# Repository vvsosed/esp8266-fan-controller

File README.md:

# fan_controller

ESP8266 firmware that drives three 4-pin PWM PC fans from a radiator's inlet temperature, meters the water flow and the heat the radiator sheds, keeps an energy total, reports each fan's RPM over serial, serves a status page over Wi-Fi, and shares its fan curve and readings over MQTT.

Hardware design, wiring and parts list: see [`docs/esp8266-fan-controller-research.md`](docs/esp8266-fan-controller-research.md).

---

## Quick reference

Run all commands from inside the sketch folder.

| Task | Command |
|---|---|
| Compile | `./build.sh` |
| Compile + flash | `./build.sh --upload` |
| Flash last build | `arduino-cli upload .` |
| Serial monitor | `arduino-cli monitor -p $PORT --config baudrate=115200` |
| Export `.bin` to `./build` | `./build.sh -e` |
| Clean rebuild | `./build.sh --clean` |
| Find connected boards | `arduino-cli board list` |
| Update cores/libraries | `arduino-cli update && arduino-cli upgrade` |

These short forms work after the one-time `board attach` step in [Setup](#4-attach-board-and-port-to-the-sketch). Without it, add `-b $FQBN` (and `-p $PORT` for upload).

`./build.sh` writes the current git commit into `git_hash.h`, then runs `arduino-cli compile` with any extra arguments you give it. The commit shows in the status page footer. Plain `arduino-cli compile .` also builds, but the footer then shows `unknown`, or the commit from the last `./build.sh` run.

---

## Project layout

```
fan_controller/
├── fan_controller.ino   # firmware (folder and .ino names must match)
├── build.sh             # stamps the git commit into git_hash.h, then compiles
├── git_hash.h           # generated by build.sh; not committed
├── sketch.yaml          # default board + port, created by `board attach`; not committed
├── README.md
├── CLAUDE.md            # guidance for Claude Code
├── .gitignore
├── docs/
│   ├── esp8266-fan-controller-research.md   # hardware design, wiring, parts list
│   └── board/           # perfboard placement plan for a bare ESP-12F: `python3 page.py` regenerates board.html
├── hardware/
│   └── kicad/           # KiCad 10 project, generated: schematic, two-layer PCB, fab files in out/ (`python3 gen.py`)
├── mqtt-broker/         # throwaway Mosquitto in Docker for testing MQTT (Dockerfile + entrypoint.sh)
└── build/               # only if you export binaries (-e); not committed
```

---

## Hardware summary

| Signal | GPIO | Board label | Notes |
|---|---|---|---|
| PWM, all three fans | 12 | D6 | One NPN/MOSFET open-drain stage feeds every fan's pin 4, like a PWM splitter (inverted in firmware) |
| Fan 1 / 2 / 3 tach | 5 / 4 / 14 | D1 / D2 / D5 | 10 kΩ pull-up to **3.3 V** |
| Inlet and outlet DS18B20s, data | 2 | D4 | Both on one 1-Wire bus, 4.7 kΩ pull-up to 3.3 V. Which is which is set on the status page ([water loop](#water-loop-flow-heat-and-energy)) |
| Flow meter pulses | 13 | D7 | The meter runs on 12 V and its pulses swing that high, so they go through an inverting NPN: 10 kΩ into the base, collector to D7 with a 10 kΩ pull-up to 3.3 V. The firmware also enables D7's internal pull-up, so a disconnected pin counts nothing |
| Fans' 12 V switch | 16 | D0 | NPN + P-MOSFET high-side switch, 10 kΩ pull-up to 3.3 V. High or undriven = fans powered |

Fans run on a separate 12 V supply, switched on and off by D0 ([wiring](docs/esp8266-fan-controller-research.md#5-wiring-per-channel)). The flow meter takes its 12 V before that switch, so it keeps counting with the fans off. All grounds must be common.

D8 (GPIO15) is the only free pin. It must be low at boot, so nothing wired to it may pull it high.

---

## Ordering the PCB

`hardware/kicad/` is a KiCad 10 project with the controller's schematic and a two-layer 70 × 50 mm board: the circuit of the
[perfboard plan](https://vvsosed.github.io/esp8266-fan-controller/board/board.html) built around a bare ESP-12F, plus two
protections the perfboard never had, a resettable fuse on the 12 V input and a reverse-polarity diode behind it. Everything
there is generated by scripts, and the committed files are the current output, so ordering needs no KiCad.

**To order**: upload `hardware/kicad/out/gerbers.zip` (Gerbers, drill file and job file) to any two-layer service, such as
JLCPCB, PCBWay or Aisler, and take the defaults: 2 layers, 1.6 mm FR-4, any finish, any mask colour. The design keeps
0.25 mm clearance, 0.3 mm tracks and 0.8/0.4 mm vias, two to three times every basic service's minimum, so no option needs
changing.

**To populate**: `hardware/kicad/out/bom.csv` lists every part, and `out/board-top.png`, `out/board-bottom.png` and
`out/schematic.pdf` show where it goes. Beyond the [parts list](docs/esp8266-fan-controller-research.md#6-parts-list), the
bare ESP-12F and the Mini-360 buck module (set it to 3.3 V before it goes in) that the perfboard plan already uses, buy an
MF-R250 polyfuse (2.5 A hold, radial, 5.1 mm lead pitch) for F1 and a 1N5401 (3 A, DO-201AD) for D2. D2 sits across the
fused input, so a reversed supply trips the fuse instead of the board. The silkscreen names every header pin and marks the
diodes' cathodes.

**To change it**: the circuit lives in `docs/board/data.py` (the netlist is derived from the perfboard plan) and every
position, track and label in `hardware/kicad/layout.py`. `python3 hardware/kicad/gen.py` regenerates the project, runs ERC
and DRC and rewrites `out/` (`--quick` skips the exports); it needs KiCad 10 with its Python module and `kicad-cli` on the
path. `python3 -m unittest discover -s hardware/kicad/tests` runs the checks. Open `hardware/kicad/fan_controller.kicad_pro`
in KiCad to look around, but don't edit the generated files: the next run overwrites them.

---

## Setup (once per machine, Manjaro / Arch)

### 1. Install Arduino CLI and get serial port access

```bash
sudo pacman -S arduino-cli
sudo usermod -aG uucp $USER   # log out and back in afterwards
groups                        # should now list uucp
```

### 2. Install the ESP8266 core

```bash
arduino-cli config init
arduino-cli config add board_manager.additional_urls \
  https://arduino.esp8266.com/stable/package_esp8266com_index.json
arduino-cli core update-index
arduino-cli core install esp8266:esp8266
```

### 3. Install libraries

```bash
arduino-cli lib install OneWire DallasTemperature WiFiManager@2.0.17 PubSubClient@2.8.0
```

### 4. Attach board and port to the sketch

Set the board and port for your hardware:

```bash
export FQBN=esp8266:esp8266:d1_mini:xtal=160,baud=921600   # NodeMCU: esp8266:esp8266:nodemcuv2:...
export PORT=/dev/ttyUSB0                                   # check with: arduino-cli board list
```

| FQBN option | Meaning |
|---|---|
| `xtal=160` | CPU at 160 MHz (smoother software PWM) |
| `baud=921600` | Upload speed; use `115200` if uploads fail |
| `wipe=all` | Erase the entire flash on upload (use only when needed) |

List every option your board supports:

```bash
arduino-cli board details -b esp8266:esp8266:d1_mini
```

Save board and port into `sketch.yaml` so later commands need no flags:

```bash
arduino-cli board attach -p $PORT -b $FQBN .
```

### 5. Resolve `.local` names

The board announces itself over mDNS. Linux resolves `.local` names only when the Avahi daemon runs and `nss-mdns` is hooked into name lookup. Manjaro usually ships both packages with the daemon disabled.

```bash
sudo pacman -S --needed avahi nss-mdns
grep '^hosts' /etc/nsswitch.conf      # must contain: mdns_minimal [NOTFOUND=return] before resolve
sudo systemctl enable --now avahi-daemon
getent hosts fan-controller-XXXXXX.local   # prints its IP once your PC and the board share a network
avahi-browse -rt _http._tcp                # lists every board on the network with its name and IP
```

If the `hosts:` line lacks `mdns_minimal`, edit it to look like this:

```
hosts: mymachines mdns_minimal [NOTFOUND=return] resolve [!UNAVAIL=return] files myhostname dns
```

Run the `sudo` lines in a normal terminal. Claude Code's `!` prefix can't answer the password prompt.

---

## Everyday tasks

### Compile

```bash
./build.sh                       # add -v for full compiler output
```

The build summary at the end shows flash and RAM usage.

### Flash

```bash
./build.sh --upload              # compile and flash in one step
arduino-cli upload .             # flash the last build without recompiling
```

Close the serial monitor first, because it holds the port.

### Serial monitor

```bash
arduino-cli monitor -p $PORT --config baudrate=115200
```

Exit with `Ctrl+C`. Expected output, once per second:

```
#3 +12.004 2026-10-19 03:12:58 In 31.2 Out 29.8 °C 2.10 L/min 280 W -> 60 % | Fan1 840 RPM Fan2 812 RPM Fan3 865 RPM
```

Each line starts with the boot number and the seconds since boot, then the local date and time once the board has the [time from the internet](#clock-and-timestamps). Then the inlet and outlet temperatures (a missing sensor prints `-127.0`), the flow, the heat (`-- W` until both sensors read) and the duty the curve gave.

A burst of garbage right after reset is normal: the ESP8266 bootloader prints at 74880 baud.

Lines starting with `*wm:` come from WiFiManager. Once the board joins your router it prints where to find the [status page](#wi-fi):

```
Web UI: http://192.168.1.42/  (http://fan-controller-1a2b3c.local/)
```

### Get the compiled binary

By default, builds go to the cache at `~/.cache/arduino/sketches/<HASH>/fan_controller.ino.bin` (older CLI versions use `/tmp/arduino/sketches/<HASH>/`).

```bash
./build.sh -e                             # copy binaries to ./build/<fqbn>/
./build.sh --output-dir ./out             # copy binaries to a directory of your choice
arduino-cli compile --show-properties . | grep '^build.path'   # print the cache path
```

To always export binaries:

```bash
arduino-cli config set sketch.always_export_binaries true
```

### Flash a `.bin` with esptool directly

This is useful for flashing a saved build without the sketch.

```bash
sudo pacman -S esptool
esptool.py --port $PORT --baud 460800 write_flash 0x0 build/*/fan_controller.ino.bin
```

### Flash over Wi-Fi from the browser

Once the board is on your network, it doesn't need the USB cable:

1. Run `./build.sh -e`. Commit first if you want a clean hash in the [footer](#status-page).
2. On the status page, open **Info / erase Wi-Fi** → **Update**, choose `build/esp8266.esp8266.d1_mini/fan_controller.ino.bin` and press **Update**.
3. The page says `Update successful. Device rebooting now...`, waits until the board answers again (about 20 s), then opens the status page. Check the version in the footer.

The fans run at 100 % during the reboot. The saved curve and Wi-Fi settings are kept. If the board isn't back within a minute, press RST once (twice opens the setup access point).

### Erase the flash completely

Use this before flashing if the board behaves oddly after flashing other firmware.

```bash
esptool.py --port $PORT erase_flash
# or, through Arduino CLI, during upload:
arduino-cli upload -b $FQBN,wipe=all -p $PORT .
```

### Identify the chip and flash size

```bash
esptool.py --port $PORT flash_id
```

### Change the fan curve

Use the form on the [status page](#status-page), or [MQTT](#mqtt): duty ramps linearly from the low % at the low temperature to the high % at the high temperature, and is clamped outside that range. **Save** applies it on the next 1 s cycle and stores it in flash, so it survives reboots. **Defaults** restores the values compiled into the firmware.

| Field | Default | Allowed |
|---|---|---|
| Ramp start / end (°C) | 21 / 30 | 0–100, start below end |
| Duty at start / end (%) | 20 / 100 | 0–100, start ≤ end, end at least 1 (0 → 0 % would keep the fans switched off) |

The defaults are `DEFAULT_CURVE` in `fan_controller.ino`:

```cpp
const Curve DEFAULT_CURVE = {21, 30, 20, 100};   // tLow °C, tHigh °C, pctMin %, pctMax %
```

Editing them only matters until a curve has been saved from the page; after that the saved curve wins until you press **Defaults** (or flash with `wipe=all`).

A missing inlet sensor and the boot period always run the fans at 100 % (`PCT_FAILSAFE`), even if the curve's maximum is lower.

### Water loop: flow, heat and energy

Two DS18B20s on the same 1-Wire bus measure the radiator's inlet (the warm water from the PC) and its outlet, and a Hall-effect flow meter (a YF-S401 or similar) counts the water through it. From those the board shows:

- **Heat**, in W: what the radiator sheds, `heat capacity × flow / 60 × (inlet − outlet)`. Positive while the water comes in warmer than it leaves; `—` on the page and `null` in the JSON while either sensor is missing.
- **Energy**, in kWh: the heat summed since the last **Reset** on the status page, which also shows when that was. It survives restarts, firmware updates and power cuts: the total goes to RTC memory every second and to a flash log of its own once an hour and on Reset, so a power cut loses under an hour of it. Serial prints `Energy: 123 Wh, from RTC` (or `from flash`) at boot and `Energy: reset` on Reset.
- **Flow**, in L/min.

The fan curve follows the **inlet**. Which physical sensor plays which role is a saved setting: the first sensor the board ever finds becomes the inlet, so a board upgraded with one sensor keeps regulating on it, and the next one found becomes the outlet. Open **Loop** on the status page to see both sensors' addresses, and press **Swap inlet/outlet** if they are the wrong way round. A missing inlet runs the fans at 100 %, as a missing sensor always has; a missing outlet only blanks the heat. While a sensor is missing the board looks at the bus once a minute, and a sensor it has never seen takes the vacant role: a newly plugged or replaced sensor is picked up without a reboot, while a sensor that is merely unplugged keeps its role until it is back. Serial prints the roles at boot and after every change: `Loop: 4186 J/(L·K), 5880 pulses/L; inlet 28ff…, outlet 28ff…`.

**Loop** also holds the two numbers the heat depends on. **Save** stores them in flash:

| Field | Default | Allowed | Notes |
|---|---|---|---|
| Water, J/(L·K) | 4186 | 100–20000 | The coolant's heat capacity per litre: water 4186, a 30 % glycol mix about 3900. Per litre, because the meter measures litres, so density is already in it |
| Flow meter, pulses/L | 5880 | 10–65535 | The YF-S401's figure; clones vary. To calibrate, run a measured amount of water through the meter at a steady rate while timing it, and compare the amount the board's flow implies (L/min × minutes) with what you measured: new value = old value × implied ÷ measured |
| Outlet offset, °C | 0 | −5 to 5 | Added to the outlet reading everywhere: page, JSON, serial, graphs and the heat. Two sensors rarely agree to better than 0.5 °C, and at 2 L/min each 0.1 °C of disagreement is 14 W of false heat. To set it, tape the two sensors together or put both in one glass of water, wait a minute for the readings to settle, and press **Match outlet to inlet**: the board saves the smoothed difference of the last cycles, so the heat reads zero while the two are at one temperature |

Over [MQTT](#mqtt) the readings travel in `status` (`tin`, `tout`, `flow`, `heat`, `wh`, `since`). For Home Assistant's energy dashboard, `wh / 1000` makes a `kWh` sensor with `device_class: energy` and `state_class: total`, with `last_reset` taken from `since`. Not `total_increasing`: the total is signed and falls while the heat is negative, which Home Assistant would take for a meter reset and count twice. The loop settings have no MQTT topics.

**Fans fully off.** Most fans don't stop at 0 % PWM; they drop to a minimum speed instead. So when the curve gives 0 %, the firmware switches off the fans' 12 V through D0:

- **When it happens:** set **Duty at start** to 0 %. The curve works in whole degrees and rounds, so the duty leaves 0 % at the first whole degree where it reaches 1 %. With ramp start 22 °C that's 23 °C. A very flat curve, rising less than ½ % per degree (say 22–80 °C → 0–20 %), leaves 0 % a degree or more later.
- **On:** the 12 V comes back on in the next 1 s cycle once the duty is above 0.
- **Off:** the temperature has to fall 0.5 °C below that point (`POWER_HYST_C`; below 22.5 °C in the example) and stay there for 10 s straight (`POWER_OFF_DELAY_S`). In between, the fans keep running at their minimum speed. Without this, sensor noise right at the threshold would switch the fans on and off.
- **Sensor glitch:** a failed reading runs the fans at 100 % for that one second only; then they're off again.

---

## Wi-Fi

Your network's name and password are never in the source. WiFiManager stores them in the ESP's own flash.

### First-time setup

1. Flash the board. With no network saved, it starts an access point named `fan-controller-XXXXXX`, where `XXXXXX` is its chip ID. The board answers to that name on the access point and on your network alike (`http://fan-controller-XXXXXX.local/`), so note it down. Every board gets its own name, so several can share one network.
2. Join it from a phone or laptop. The password is `AP_PASS` in `fan_controller.ino` (default `fancontrol`).
3. A setup page opens by itself (otherwise browse to `http://fan-controller-XXXXXX.local/` or `http://192.168.4.1/`). Pick your network, enter its password, Save.
4. The access point shuts down and the board joins your router. Serial prints the `Web UI:` line.

The fans keep following the temperature the whole time the access point is up.

### Status page

Open `http://fan-controller-XXXXXX.local/`, the same name as the setup access point (needs [mDNS on your PC](#5-resolve-local-names)), or the IP from serial. The page title and footer show the board's name. It shows the inlet and outlet temperatures, the flow, the heat and the fan duty, the energy total with its Reset button, and each fan's RPM, updating every 2 s, two graphs of the last hour, the [fan curve](#change-the-fan-curve) form, the [water loop](#water-loop-flow-heat-and-energy) settings, the [MQTT](#mqtt) broker settings, and links to the pages below. When the 12 V is [switched off](#change-the-fan-curve), the status line says `fans off`. The last two lines show the [uptime, boots and crashes](#uptime-boots-and-crashes).

**The graphs:**
- The first: inlet (red) and outlet (pale red) on the left °C axis, duty (blue) on the right % axis, as 10-second averages. Dashed lines mark the curve's ramp start and end temperatures.
- The second: heat (purple, W, left axis) and flow (green, L/min, right axis). Both axes fit the data and always include 0, where the heat axis has a dashed line.
- Gaps mean a sensor wasn't read; the heat line needs both.
- The history is kept in the board's RAM, so it starts empty after every reboot or flash.
- Inside the ramp, duty follows the inlet temperature linearly, so those two lines often lie on top of each other. They separate where the duty is clamped at its minimum or maximum.

| Page | Use |
|---|---|
| `/history.json` | The graph data, oldest first: `{"step":10,"tl":21,"th":30,"t":[31.2,null,…],"t2":[29.8,…],"w":[280,null,…],"f":[2.10,…],"d":[60,100,…]}` (`t` inlet, `t2` outlet, `w` heat W, `f` flow L/min, `d` duty; `null` = no reading in that interval) |
| `/status.json` | The live numbers as JSON, e.g. `{"t":31.2,"tin":31.2,"tout":29.8,"flow":2.10,"heat":280,"wh":12345,"since":1792300000,"pct":60,"pwr":1,"rpm":[600,630,660],"up":273600,"time":1792368764,"boots":14,"booted":1792095164,"reset":"power on","crashes":1,"crash":{"at":1792090000,"up":86400,"why":"exception"}}` (`t` is the inlet, which the curve follows, and `null` when that sensor is missing, as `tout` is for the outlet; `heat` is `null` while either is; `wh` is the [energy total](#water-loop-flow-heat-and-energy) in Wh and `since` its last Reset, `null` if the clock wasn't set then; `pwr` is 0 while the fans' 12 V is off; the rest is [uptime, boots and crashes](#uptime-boots-and-crashes) and the [clock](#clock-and-timestamps)) |
| `/wifi` | Switch to a different network |
| `/info` | Chip details, and **Erase WiFi config** to forget the network (the board reboots into setup) |
| `/update` | Upload new firmware ([Flash over Wi-Fi](#flash-over-wi-fi-from-the-browser)) |

The footer shows what's running, e.g. `Firmware v0.0.1 · 37454aa`:

- **The version** is `FW_VERSION` at the top of `fan_controller.ino`. Bump it by hand when you release.
- **The commit** comes from `./build.sh`. A `-dirty` suffix means the build included uncommitted changes. To show a clean hash, commit first and then flash.

### Uptime, boots and crashes

To watch how stable the board is, the status page's last two lines show e.g.:

```
Up 3 d 04:12 since 16.10.2026, 10:01 · boots 14 · last reset: power on
Crashes 1 · last 15.10.2026, 07:40, exception after 1 d 00:00 up
```

[`/status.json`](#status-page) carries the same as `up` (seconds since this start), `time`, `boots`, `booted`, `reset`, `crashes` and `crash`. Over [MQTT](#mqtt), `up` and `time` come with the live numbers in `status`, and the other five, which describe this start, in the retained `boot` topic. Serial prints them at boot, e.g. `Boot 15, 2 crashes; this one: exception after 2 d 17:11:05 up, at 2026-10-19 03:12:44`.

- **boots** counts every start, this one included: power-ons, resets, firmware updates and crashes. Counting begins with the first firmware that has the counter. Only [erasing the flash completely](#erase-the-flash-completely) sets it back to 0.
- **booted** is when this start happened, in UTC seconds. It is `null` until the board first gets the [time](#clock-and-timestamps), and from then on it is that time minus the uptime.
- **crashes** counts the starts that followed a crash. This is the number to watch.
- **last crash** (`crash` in the JSON, `null` before the first) says when it happened (`at`, UTC seconds), how long the board had been up (`up`, seconds) and why (`why`, one of the crash causes below). `at` is `null` if the board crashed before it had the [time](#clock-and-timestamps). It is kept with the count, so it survives later restarts and power cuts. Both come from a note the board makes in reset-proof memory every second, so they are right to within a second or two, a few seconds if an MQTT connect was under way.
- **after … up** on the serial boot line is how long the previous run lasted. It is missing after a power cut, which wipes that memory.
- **last reset** says why this start happened:

| `reset` | Cause |
|---|---|
| `power on` | The board got power. One that nobody caused means the supply dropped out |
| `reset pin` | The RST button, or a USB serial upload |
| `restart` | The firmware restarted itself: after a [firmware update over Wi-Fi](#flash-over-wi-fi-from-the-browser), when the setup access point [timed out](#getting-back-into-setup), or after **Erase WiFi config** |
| `exception` | Crash: the program hit a CPU exception, e.g. a bad pointer |
| `software watchdog`, `hardware watchdog` | Crash: the program got stuck |
| `panic` | Crash: abort, failed assert, or out of memory |

**Where the count is kept.** Each start adds a small record to a log in two flash sectors of their own, at the end of the 2 MB filesystem area. This firmware has no filesystem, and firmware updates don't write there. The fan curve, broker and loop settings live elsewhere and are still written only when you save them. The [energy total](#water-loop-flow-heat-and-energy) has a log of the same kind in the two sectors below the counter's.

- **Wear:** a record goes into erased flash, so most starts erase nothing. A sector is erased once every 170 starts. Even a crash every 5 s would erase each sector only about twice an hour, years before typical flash (100,000 erases) wears out.
- **Power cuts:** a power cut while a record is being written loses that one start, nothing more.
- **Other flash layouts:** the counter needs the board's default layout, `4MB (FS:2MB …)`. Built with `FS:none`, it shows only the current start (`boots 1`), and serial says `Boot counter off`. If you ever add a filesystem to this firmware, keep it clear of its last four sectors.

**Watching it over MQTT.** Subscribe to `…/boot`. Being retained, it arrives as soon as you subscribe, again each time the board connects to the broker, and once more when the board first gets the time, to add `booted`. A rising `crashes` means a crash; a rising `boots`, or a falling `up` in `status`, means some restart.

**Finding the cause of a crash.** Serial prints the crash before the board restarts: `Exception (n)`, `Soft WDT reset`, `Panic …` or `Abort called`, then a stack dump between `>>>stack>>>` and `<<<stack<<<`. Turn the code addresses (`40xxxxxx`) into source lines with the `.elf` of the same build (`./build.sh -e` exports it):

```bash
~/.arduino15/packages/esp8266/tools/xtensa-lx106-elf-gcc/*/bin/xtensa-lx106-elf-addr2line -pfiaC \
  -e build/esp8266.esp8266.d1_mini/fan_controller.ino.elf 0x40201588 0x40203f2c   # addresses from the dump
```

### Clock and timestamps

The board keeps two kinds of time:

- **Boot number and uptime** (`#14 +3612.345` on serial, `boots` and `up` in the JSON; over MQTT `boots` is in `boot` and `up` in `status`). They never jump and need no network, so use them to put events in order and to measure how long things took. The boot number survives power cuts; the uptime starts at 0 on every boot.
- **The clock** (the date and time on serial, `time` in the JSON as UTC seconds). The board gets it from `pool.ntp.org` (`NTP_SERVER`) a few seconds after joining your network, and serial prints `Time: synced (booted …)`. It is corrected every hour. The clock can jump, at that first sync and by a fraction of a second at each correction. Nothing that drives the fans uses it.

The board's start time is `booted`: `time` − `up` at the first sync. Until then, and always in setup mode or without internet access, there is no clock: `time` and `booted` are `null`, the page leaves out `since`, and serial lines show only boot number and uptime. Your router probably doesn't serve the time itself, so the board needs internet access.

**Timezone.** `TIMEZONE` at the top of `fan_controller.ino` is a POSIX TZ string, set for Kyiv. The ESP8266 core's `TZ.h` (in `~/.arduino15/packages/esp8266/hardware/esp8266/*/cores/esp8266/`) lists them for other places. It only affects serial: the page shows your browser's local time, and the JSON and MQTT carry UTC.

Lines printed by WiFiManager itself (`*wm:`) have no stamp.

### Getting back into setup

- **Automatically:** if the saved network can't be reached at boot, the board tries for 20 s (fans at 100 %), then opens the setup access point for 3 minutes, then restarts and tries again. The access point stays up while a device is joined to it.
- **Double reset:** press RST, then press it again within 10 s. The setup access point opens with the same 3-minute timeout. Unplugging power doesn't count; it must be the RST button.

The timeouts are `CONNECT_TIMEOUT_S` and `PORTAL_TIMEOUT_S` at the top of `fan_controller.ino`.

### MQTT

The board can publish its fan curve and readings to an MQTT broker and take curve changes from it. It stays off until you enter a broker.

**Setup.** On the [status page](#status-page), open **MQTT** and enter the broker's IP or DNS name and port (1883 by default). If the broker needs a login, add the user and password. Then press **Save**. The section's title shows the state: `connected`, `not connected (state N)` or `off`. Serial also prints `MQTT: connected to …`.

- **Use an IP or a DNS name.** A `.local` name doesn't work, because the ESP8266 can't resolve mDNS names when it connects out.
- **Password field:** leave it blank to keep the saved password. That only works while the broker and the user stay the same. If you change either, enter the password again, so the old password is never sent to a new broker. Clearing the user removes both.
- **Broker unreachable:** the board tries again after 30 s and doubles the wait after each failure, up to 5 min (`MQTT_RETRY_MIN_S` / `MQTT_RETRY_MAX_S`). Each try can freeze the status page for up to about 6 s. The fans keep running normally. Saving the MQTT form tries again at once, and so does a connection that drops after it was working.

**Detach.** To switch MQTT off, press **Detach** in the MQTT section. The board publishes `offline`, then erases its retained topics on the broker (`ramp`, `duty`, `boot` and `online`), so the device no longer shows up there. Then it disconnects and forgets the broker, user and password. Saving with the broker field blank does the same. Saving a different broker or port erases the topics on the old one before connecting to the new one. Saving the same broker again (a new password, say) only sends `offline` and reconnects.

The board can only erase while it is connected, and it waits up to 1 s for the broker to confirm. If it isn't connected, or there is no reply, it still detaches, but a page says that its topics on that broker may be left behind. To erase them by hand, send an empty retained message to each, with the port and login the board used:

```bash
for t in ramp duty boot online; do mosquitto_pub -h <broker> -p 1883 -u <user> -P <password> -t fan-controller-XXXXXX/$t -r -n; done   # drop -u/-P without a login
```

**Topics.** Every topic starts with the board's name, the same `fan-controller-XXXXXX` as on the status page:

| Topic | Direction | Payload |
|---|---|---|
| `…/ramp` | from the board, retained | `{"low":21,"high":30}`: ramp start and end, °C |
| `…/ramp/set` | to the board | `{"low":22,"high":32}`, or one key alone: `{"low":22}` |
| `…/duty` | from the board, retained | `{"min":20,"max":100}`: duty at ramp start and end, % |
| `…/duty/set` | to the board | `{"max":80}` etc. |
| `…/status` | from the board, every 5 s (`MQTT_STATUS_S`) | The live part of [`/status.json`](#status-page): `{"t":31.2,"tin":31.2,"tout":29.8,"flow":2.10,"heat":280,"wh":12345,"since":1792300000,"pct":60,"pwr":1,"rpm":[600,630,750],"up":273600,"time":1792368764}` |
| `…/boot` | from the board, retained, each time it connects and once more when it first gets the time | The rest of `/status.json`, which describes this start: `{"boots":14,"booted":1792095164,"reset":"power on","crashes":1,"crash":{"at":1792090000,"up":86400,"why":"exception"}}` ([uptime, boots and crashes](#uptime-boots-and-crashes)) |
| `…/online` | from the board, retained | `online`, or `offline` once the board drops off (the broker sends it for the board). Erased, with the other retained topics, on [Detach](#mqtt) |

`ramp` and `duty` are the two rows of the [fan curve](#change-the-fan-curve) form.

**How a set works:**
- **Keys:** a set can carry one key or both. A missing key keeps its current value. Values must be whole numbers.
- **Applied like Save:** the board treats a set exactly like **Save** on the page. The same limits apply, the change takes effect on the next 1 s cycle, and it is stored in flash.
- **Rejected sets:** the board ignores the whole set if any of these is true, and serial prints `MQTT: ignored …`:
  - the result breaks the limits;
  - any key's value isn't a whole number, such as `99.9` or `"32"`;
  - the payload is longer than 127 bytes.
- **Both cases:** the board republishes `ramp` and `duty`, so they always show the curve in force.

**Examples.** `mosquitto_sub` and `mosquitto_pub` come with the `mosquitto` package. Add `-u <user> -P <password>` if the broker needs a login.

```bash
mosquitto_sub -h <broker> -t 'fan-controller-XXXXXX/#' -v      # watch everything
mosquitto_pub -h <broker> -t fan-controller-XXXXXX/ramp/set -m '{"low":22,"high":32}'
mosquitto_pub -h <broker> -t fan-controller-XXXXXX/duty/set -m '{"max":80}'
```

- **Don't publish sets as retained.** The broker would resend them every time the board reconnects, overwriting any change made on the page since.
- **Don't automate sets every few seconds.** Each accepted set that changes the curve rewrites the board's flash. Changes by hand, or an occasional automation, are fine. A set that changes nothing writes nothing.

**Test broker.** If you don't have a broker, `mqtt-broker/` builds a throwaway Mosquitto 2.0.22 in Docker. It uses plain TCP and keeps nothing between runs, retained messages included.

```bash
docker build -t fan-mqtt mqtt-broker
docker run --rm --name fan-mqtt -p 1883:1883 fan-mqtt                                     # no login
docker run --rm --name fan-mqtt -p 1883:1883 -e MQTT_USER=fan -e MQTT_PASS=secret fan-mqtt   # or: login required
docker exec fan-mqtt mosquitto_sub -t 'fan-controller-XXXXXX/#' -v                        # watch; add -u fan -P secret with a login
docker exec fan-mqtt mosquitto_pub -t fan-controller-XXXXXX/duty/set -m '{"max":80}'
```

On the status page, enter your PC's LAN IP as the broker (`ip -4 addr`), not `localhost`. The board connects to the PC from outside, so a firewall on the PC must allow TCP 1883. The `docker run` window logs each connection, e.g. `New client connected … as fan-controller-XXXXXX`, and each refused login (`not authorised`). Ctrl+C stops the broker.

### Security

- `AP_PASS` is committed in the source, so change it before flashing if the repo is shared. It must be at least 8 characters.
- The status and Wi-Fi pages on your LAN have no login. Anyone on your network can open them, change the fan curve, change or erase the Wi-Fi settings, and flash new firmware.
- MQTT is plain TCP, without TLS, and the broker password is stored unencrypted in the board's flash. Anyone who can publish to the broker can change the fan curve.

---

## Maintenance

```bash
arduino-cli update && arduino-cli upgrade   # refresh indexes, upgrade core + libraries
arduino-cli core list                       # installed cores and versions
arduino-cli lib list                        # installed libraries
arduino-cli cache clean                     # wipe the build cache
arduino-cli version
```

---

## Troubleshooting

| Symptom | Likely cause / fix |
|---|---|
| `Permission denied: /dev/ttyUSB0` | Not in `uucp` group yet. Run the `usermod` command from Setup, then log out and back in |
| Board missing from `board list` | Charge-only USB cable; check `dmesg -w` while plugging in (expect `ch341` or `cp210x`). If `brltty` is installed it can grab CH340 adapters: `sudo pacman -Rns brltty` |
| `Timed out waiting for packet header` | Lower upload speed (`baud=115200`). If it persists, hold FLASH and tap RESET to enter the bootloader manually |
| `Port busy` / upload fails right away | Serial monitor still open; close it |
| Board doesn't boot with hardware attached | Something wired to the free D8 (GPIO15) pulls it high (a fan's PWM line would), or GPIO0/GPIO2 held low |
| Fans always at 100 % | The inlet sensor isn't read (`In -127.0` in the log): check its wiring and the 4.7 kΩ pull-up. If the other sensor reads fine, the roles may be the wrong way round: open **Loop** on the status page and press **Swap inlet/outlet**. A replacement sensor is adopted within a minute of being plugged in, as long as the old one is gone. Also check whether the fans' PWM lines are wired straight to D6 without the transistor: then the PWM is not inverted and `setFan()` needs `analogWrite(PWM_PIN, pct * 255 / 100)` |
| Occasional single `-127.0` reading, fans jump to 100 % for a second | The firmware already retries a failed read once, because web traffic can disturb 1-Wire timing on the ESP8266. If it still shows up, check the sensor wiring, the 4.7 kΩ pull-up and the cable length |
| Heat shows `—`, `heat` is `null` | One of the two sensors isn't read; the status line and **Loop** say which. With one sensor the board still regulates the fans, but can't compute heat or add to the energy total |
| Flow stays `0.00 L/min` | No pulses reach D7: the meter has no supply (it needs 5–24 V; the board plan feeds it 12 V), its signal isn't going through the NPN stage, or no water is moving. D7 idles at 3.3 V and drops on every pulse |
| Heat wanders around 0 at idle, or reads negative | Two DS18B20s can disagree by up to 0.5 °C each, most of a radiator's temperature drop at low load. Noise averages out of the energy total; a steady offset does not, so compare the two sensors in the same water before trusting small numbers. Couple the two sensors and press **Match outlet to inlet** to cancel their disagreement (see [Water loop](#water-loop-flow-heat-and-energy)) |
| RPM reads 0 | Missing tach pull-up, fan not powered, or grounds not common. Expected while the 12 V is switched off (status page says `fans off`) |
| Fans still spin at 0 % | The 12 V is cut only once the temperature is 0.5 °C below where the duty leaves 0 %, and then after 10 s, so wait. If the status says `fans off` and they still spin, the P-MOSFET is probably reversed: its built-in diode then passes 12 V all the time. Source goes to the 12 V supply, drain to the fans |
| Fans never spin, even at 100 % | No 12 V reaches pin 2. Check that D0 measures 3.3 V while the firmware runs (about 1.5 V with the board in reset, where only the 10 kΩ pull-up holds it), the transistor pinouts (they differ between part numbers), and that the NPN emitter is grounded |
| RPM jumps around | Add a 10 kΩ external pull-up (instead of `INPUT_PULLUP`) and/or 10 nF from tach pin to GND |
| A fan reads ~760,000 RPM | Its tach pin is counting the 25 kHz PWM (760,000 ÷ 30 ≈ 25,000 pulses/s), so it's shorted to a PWM line. Look for a solder bridge between neighbouring header pins (D5 sits next to D6 on the D1 mini) or a tach wire touching the PWM transistor's collector (the shared line to every fan's pin 4). If unplugging the fan doesn't change the reading, the short is on the board |
| Wi-Fi flaky or won't connect | A tach pin shorted to PWM (row above) fires 25,000 interrupts per second and starves Wi-Fi. Fix that first |
| Setup access point appears unexpectedly | A second reset within 10 s of boot counted as a [double reset](#getting-back-into-setup). Opening the serial monitor right after flashing can do this. Press RST once and wait |
| `crashes` keeps going up | Leave a serial monitor running until it happens again, then [decode the stack dump](#uptime-boots-and-crashes). A `hardware watchdog` crash prints no dump |
| `last reset: power on`, but nobody switched it off | The board lost power. Check its 5 V supply and USB cable |
| `time` and `booted` stay `null`, serial lines show no date | The board can't reach `pool.ntp.org`: no internet access, or DNS or UDP port 123 is blocked. It never syncs in setup mode. A `.local` name in `NTP_SERVER` never works: use a DNS name or an IP |
| `fan-controller-XXXXXX.local` doesn't resolve | Check the chip ID first: `avahi-browse -rt _http._tcp` or your router's DHCP list shows each board's name. Otherwise `avahi-daemon` usually isn't running (`systemctl is-active avahi-daemon`). See [Setup step 5](#5-resolve-local-names). If it runs and still fails, a firewall may be blocking UDP 5353. Or use the IP from serial |
| Changed `DEFAULT_CURVE` and flashed, but the curve didn't change | A curve saved from the status page takes priority over the compiled defaults. Press **Defaults** on the page |
| MQTT says `not connected (state -2)` or `(state -4)` | The board can't reach the broker, or it didn't answer in time. Check the IP and port, that the broker is running, and that no firewall blocks the port (1883). A `.local` broker name never works here: use the IP |
| MQTT says `not connected (state 4)` or `(state 5)` | The broker refused the login. Re-enter the user and password (the password field is always shown blank) |
| An MQTT set changes nothing | Serial prints `MQTT: ignored …`. The values broke the [curve limits](#change-the-fan-curve), a value isn't a whole number, or the payload isn't JSON like `{"low":22}`. To move the ramp start past its current end, send both in one message: `{"low":35,"high":40}` |
| Status page unreachable after changing network | The board couldn't join the new network (wrong password, or out of range). Press RST: if the saved network still can't be reached, it falls back to the setup access point after 20 s |

---

## .gitignore

```
build/
out/
!hardware/kicad/out/
sketch.yaml
git_hash.h
```

`sketch.yaml` is ignored because its `default_port` is specific to one machine. Each
checkout creates its own with the `board attach` step in [Setup](#4-attach-board-and-port-to-the-sketch),
or passes `-b $FQBN` and `-p $PORT` explicitly.

`git_hash.h` is ignored because `./build.sh` regenerates it on every build, and a commit can't contain its own hash.

`hardware/kicad/out/` is kept, so the fab files can be ordered from a checkout, except `out/gerbers/`, which `gen.py` zips into the
committed `out/gerbers.zip`. KiCad's own backups, caches and lock files are ignored too.

## License

MIT, see [LICENSE](LICENSE).

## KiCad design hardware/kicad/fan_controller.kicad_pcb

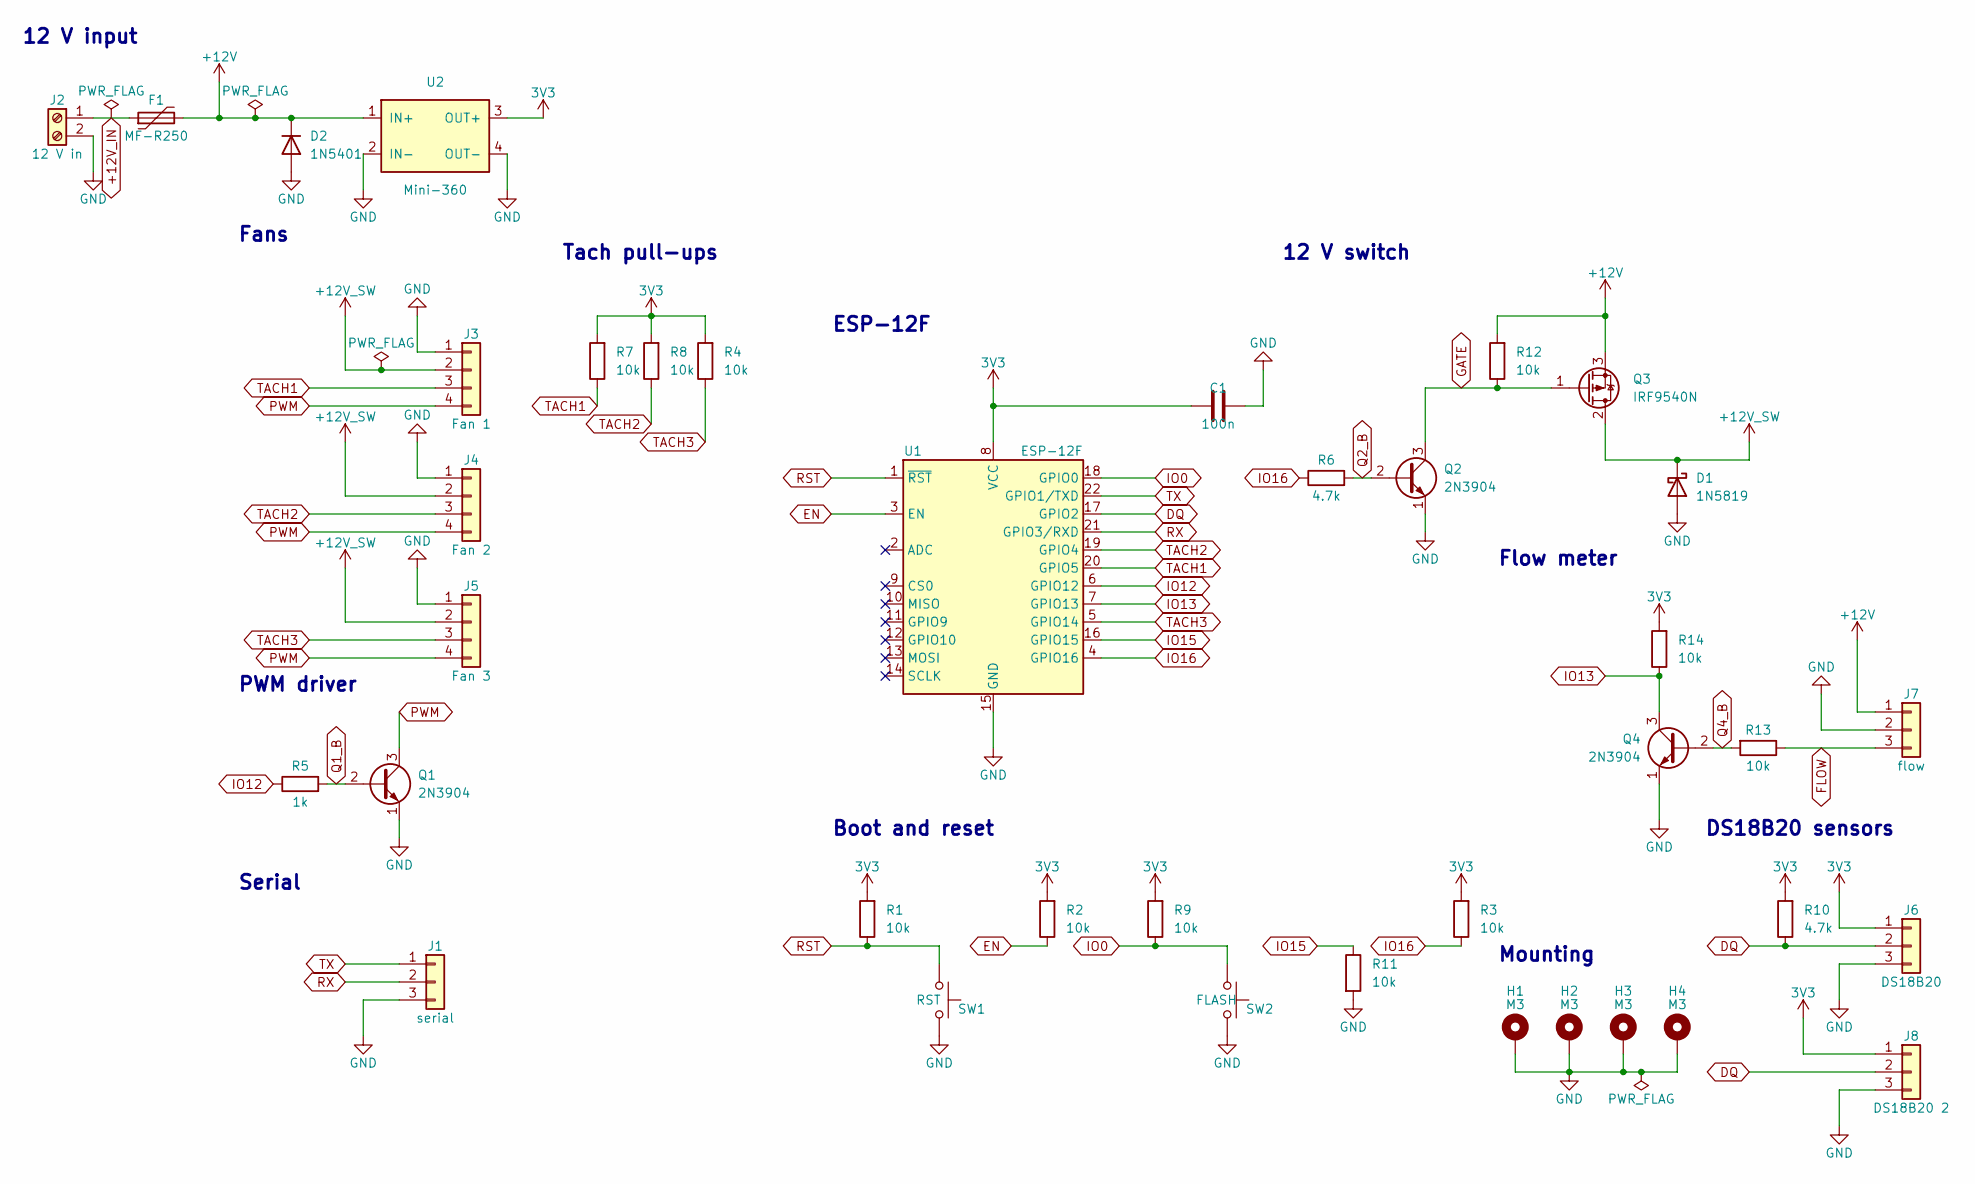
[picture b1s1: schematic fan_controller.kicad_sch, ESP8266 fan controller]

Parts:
C1: 100n; C_Disc_D5.0mm_W2.5mm_P2.50mm
D1: 1N5819; D_DO-41_SOD81_P7.62mm_Horizontal
D2: 1N5401; D_DO-201AD_P12.70mm_Horizontal
F1: MF-R250; Polyfuse_Radial_P5.1mm
H1, H2, H3, H4: M3; MountingHole_3.2mm_M3_DIN965_Pad
J1: serial; PinHeader_1x03_P2.54mm_Vertical
J2: 12 V in; TerminalBlock_Phoenix_MKDS-1,5-2-5.08_1x02_P5.08mm_Horizont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
J3: Fan 1; Molex_KK-254_AE-6410-04A_1x04_P2.54mm_Vertical
J4: Fan 2; Molex_KK-254_AE-6410-04A_1x04_P2.54mm_Vertical
J5: Fan 3; Molex_KK-254_AE-6410-04A_1x04_P2.54mm_Vertical
J6: DS18B20; PinHeader_1x03_P2.54mm_Vertical
J7: flow; PinHeader_1x03_P2.54mm_Vertical
J8: DS18B20 2; PinHeader_1x03_P2.54mm_Vertical
Q1, Q2, Q4: 2N3904; TO-92_Inline_Wide
Q3: IRF9540N; TO-220-3_Vertical
R1, R2, R4, R7, R8, R9, R11, R12, R13, R14: 10k; R_Axial_DIN0207_L6.3mm_D2.5mm_P7.62mm_Horizontal
R3: 10k; R_Axial_DIN0207_L6.3mm_D2.5mm_P2.54mm_Vertical
R5: 1k; R_Axial_DIN0207_L6.3mm_D2.5mm_P7.62mm_Horizontal
R6, R10: 4.7k; R_Axial_DIN0207_L6.3mm_D2.5mm_P7.62mm_Horizontal
SW1: RST; SW_PUSH_6mm
SW2: FLASH; SW_PUSH_6mm
U1: ESP-12F; ESP-12E
U2: Mini-360

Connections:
3V3: C1.1, J6.1, J8.1, R1.2, R2.2, R3.2, R4.2, R7.2, R8.2, R9.2, R10.2, R14.2, U1.8 (VCC), U2.3 (OUT+)
+12V: D2.1 (K), F1.2, J7.1, Q3.3 (S), R12.2, U2.1 (IN+)
+12V_IN: F1.1, J2.1
+12V_SW: D1.1 (K), J3.2, J4.2, J5.2, Q3.2 (D)
DQ: J6.2, J8.2, R10.1, U1.17 (GPIO2)
EN: R2.1, U1.3 (EN)
FLOW: J7.3, R13.1
GATE: Q2.3 (C), Q3.1 (G), R12.1
GND: C1.2, D1.2 (A), D2.2 (A), H1.1, H2.1, H3.1, H4.1, J1.3, J2.2, J3.1, J4.1, J5.1, J6.3, J7.2, J8.3, Q1.1 (E), Q2.1 (E), Q4.1 (E), R11.2, SW1.2, SW2.2, U1.15 (GND), U2.2 (IN-), U2.4 (OUT-)
IO0: R9.1, SW2.1, U1.18 (GPIO0)
IO12: R5.1, U1.6 (GPIO12)
IO13: Q4.3 (C), R14.1, U1.7 (GPIO13)
IO15: R11.1, U1.16 (GPIO15)
IO16: R3.1, R6.1, U1.4 (GPIO16)
PWM: J3.4, J4.4, J5.4, Q1.3 (C)
Q1_B: Q1.2 (B), R5.2
Q2_B: Q2.2 (B), R6.2
Q4_B: Q4.2 (B), R13.2
RST: R1.1, SW1.1, U1.1 (~RST)
RX: J1.2, U1.21 (GPIO3/RXD)
TACH1: J3.3, R7.1, U1.20 (GPIO5)
TACH2: J4.3, R8.1, U1.19 (GPIO4)
TACH3: J5.3, R4.1, U1.5 (GPIO14)
TX: J1.1, U1.22 (GPIO1/TXD)

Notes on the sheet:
ESP-12F
12 V input
Serial
DS18B20 sensors
Boot and reset
PWM driver
Mounting
Fans
Tach pull-ups
12 V switch
Flow meter

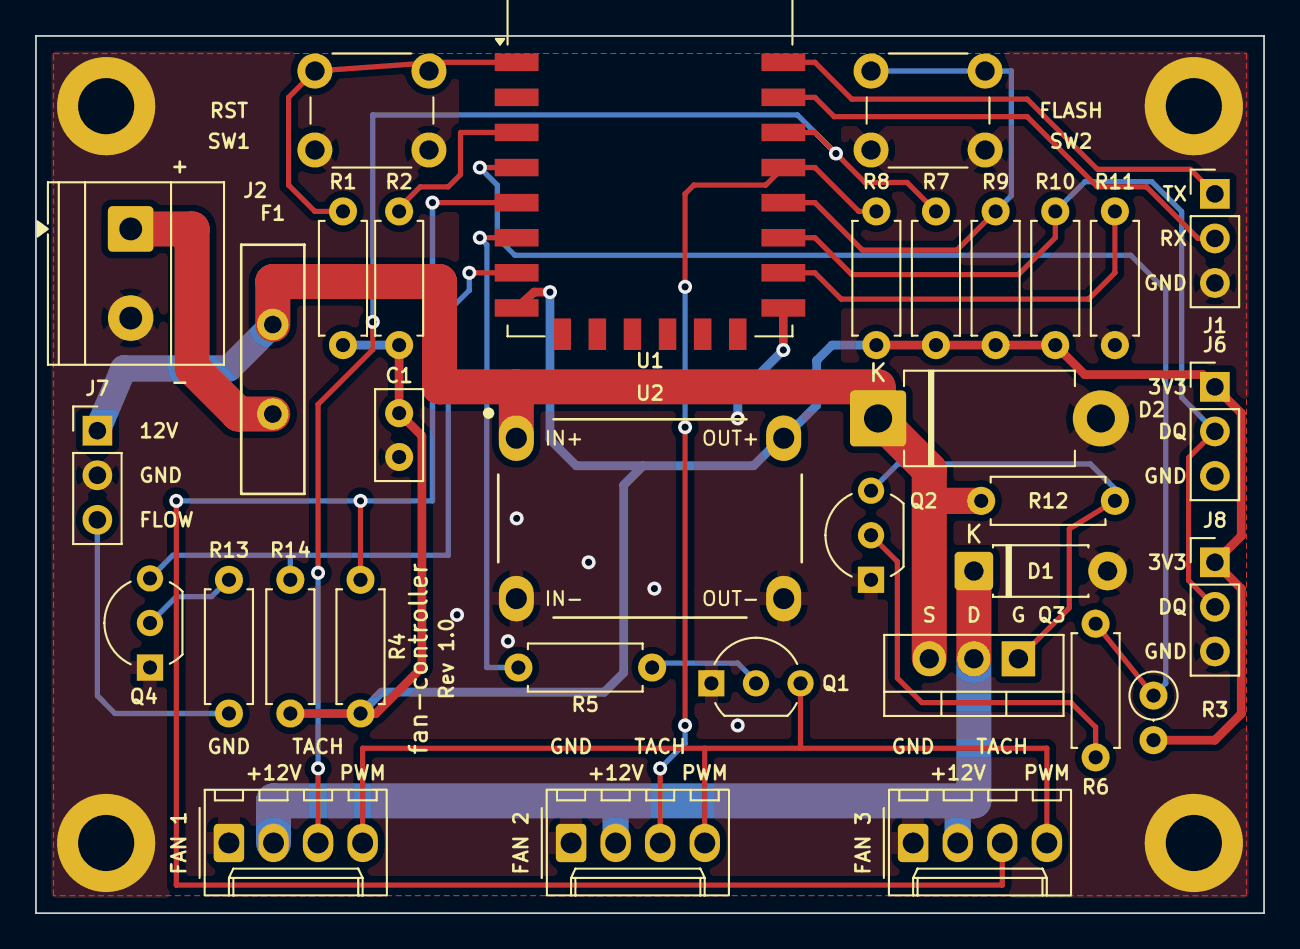
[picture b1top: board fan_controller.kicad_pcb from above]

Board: 2 copper layers, 70.0 x 50.0 mm, 38 parts (0 on the bottom side), 24 nets.

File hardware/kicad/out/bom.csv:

"Refs","Value","Footprint","Qty"
"C1","100n","Capacitor_THT:C_Disc_D5.0mm_W2.5mm_P2.50mm","1"
"D1","1N5819","Diode_THT:D_DO-41_SOD81_P7.62mm_Horizontal","1"
"D2","1N5401","Diode_THT:D_DO-201AD_P12.70mm_Horizontal","1"
"F1","MF-R250","fan_controller:Polyfuse_Radial_P5.1mm","1"
"J1","serial","Connector_PinHeader_2.54mm:PinHeader_1x03_P2.54mm_Vertical","1"
"J2","12 V in","TerminalBlock_Phoenix:TerminalBlock_Phoenix_MKDS-1,5-2-5.08_1x02_P5.08mm_Horizontal","1"
"J3","Fan 1","Connector_Molex:Molex_KK-254_AE-6410-04A_1x04_P2.54mm_Vertical","1"
"J4","Fan 2","Connector_Molex:Molex_KK-254_AE-6410-04A_1x04_P2.54mm_Vertical","1"
"J5","Fan 3","Connector_Molex:Molex_KK-254_AE-6410-04A_1x04_P2.54mm_Vertical","1"
"J6","DS18B20","Connector_PinHeader_2.54mm:PinHeader_1x03_P2.54mm_Vertical","1"
"J7","flow","Connector_PinHeader_2.54mm:PinHeader_1x03_P2.54mm_Vertical","1"
"J8","DS18B20 2","Connector_PinHeader_2.54mm:PinHeader_1x03_P2.54mm_Vertical","1"
"Q1,Q2,Q4","2N3904","Package_TO_SOT_THT:TO-92_Inline_Wide","3"
"Q3","IRF9540N","Package_TO_SOT_THT:TO-220-3_Vertical","1"
"R1,R2,R4,R7-R9,R11-R14","10k","Resistor_THT:R_Axial_DIN0207_L6.3mm_D2.5mm_P7.62mm_Horizontal","10"
"R3","10k","Resistor_THT:R_Axial_DIN0207_L6.3mm_D2.5mm_P2.54mm_Vertical","1"
"R5","1k","Resistor_THT:R_Axial_DIN0207_L6.3mm_D2.5mm_P7.62mm_Horizontal","1"
"R6,R10","4.7k","Resistor_THT:R_Axial_DIN0207_L6.3mm_D2.5mm_P7.62mm_Horizontal","2"
"SW1","RST","Button_Switch_THT:SW_PUSH_6mm","1"
"SW2","FLASH","Button_Switch_THT:SW_PUSH_6mm","1"
"U1","ESP-12F","RF_Module:ESP-12E","1"
"U2","Mini-360","fan_controller:Mini-360","1"

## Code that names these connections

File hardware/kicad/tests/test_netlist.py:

import pathlib
import sys
import unittest

HERE = pathlib.Path(__file__).resolve().parent
sys.path.insert(0, str(HERE.parents[0]))
from netlist import NETS, PARTS, PERFBOARD


class NetlistTest(unittest.TestCase):
    def test_counts(self):
        self.assertEqual(len(PARTS), 38)
        self.assertEqual(set(NETS), {"+12V_IN", "+12V", "+12V_SW", "3V3", "GND", "RST", "EN", "IO0", "IO15", "IO16", "IO12", "IO13",
                                     "DQ", "TACH1", "TACH2", "TACH3", "TX", "RX", "PWM", "GATE", "Q1_B", "Q2_B", "Q4_B", "FLOW"})
        for net, pins in NETS.items():
            self.assertGreaterEqual(len(pins), 2, net)

    def test_fuse_and_diode(self):
        self.assertEqual(PARTS["J2"].pins, {"1": "+12V_IN", "2": "GND"})
        self.assertEqual(PARTS["F1"].pins, {"1": "+12V_IN", "2": "+12V"})
        self.assertEqual(PARTS["D2"].pins, {"1": "+12V", "2": "GND"})
        self.assertEqual(NETS["+12V_IN"], {("J2", "1"), ("F1", "1")})
        self.assertEqual(PARTS["F1"].value, "MF-R250")

    def test_module(self):
        p = PARTS["U1"].pins
        self.assertEqual({k: p[k] for k in "1 3 4 5 6 7 8 15 16 17 18 19 20 21 22".split()},
                         {"1": "RST", "3": "EN", "4": "IO16", "5": "TACH3", "6": "IO12", "7": "IO13", "8": "3V3", "15": "GND",
                          "16": "IO15", "17": "DQ", "18": "IO0", "19": "TACH2", "20": "TACH1", "21": "RX", "22": "TX"})
        self.assertTrue(all(p[k] is None for k in "2 9 10 11 12 13 14".split()))

    def test_stages(self):
        self.assertEqual(PARTS["Q1"].pins, {"1": "GND", "2": "Q1_B", "3": "PWM"})
        self.assertEqual(PARTS["Q3"].pins, {"1": "GATE", "2": "+12V_SW", "3": "+12V"})
        self.assertEqual(PARTS["Q4"].pins, {"1": "GND", "2": "Q4_B", "3": "IO13"})
        self.assertEqual(PARTS["D1"].pins, {"1": "+12V_SW", "2": "GND"})
        self.assertEqual(PARTS["J3"].pins, {"1": "GND", "2": "+12V_SW", "3": "TACH1", "4": "PWM"})
        self.assertEqual(PARTS["J7"].pins, {"1": "+12V", "2": "GND", "3": "FLOW"})
        self.assertEqual(PARTS["J6"].pins, {"1": "3V3", "2": "DQ", "3": "GND"})
        self.assertEqual(PARTS["U2"].pins, {"1": "+12V", "2": "GND", "3": "3V3", "4": "GND"})
        self.assertEqual(PARTS["SW1"].pins, {"1": "RST", "2": "GND"})
        self.assertEqual(PARTS["H1"].pins, {"1": "GND"})
        self.assertEqual(PARTS["R5"].value, "1k")
        self.assertEqual(PARTS["R10"].value, "4.7k")

    def test_perfboard_plan_is_clean(self):
        self.assertEqual(PERFBOARD.check()[0], [])


if __name__ == "__main__":
    unittest.main()
